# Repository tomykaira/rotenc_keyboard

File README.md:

# rotenc

This is PCB design and example qmk_firmware keymap implementation to add-on rotary encoders (jog dials) to your keyboards.

# Usage

Open EAGLE design file in ./pcb.
I used elecrow to print the board.
I will distribute printed PCBs by 200 JPY + shipping.

Copy keymap to qmk_firmware/keyboards/kets_split/keymaps/foobar and write.

```
make lets_split/rev2:foobar_onehanded:avrdude
```

# REFS

https://www.pixiv.net/fanbox/manage/post/104198
https://twitter.com/tomykaira_2/status/1018332701210783744

# License

keymaps: follow qmk license.
pcb design: public domain.

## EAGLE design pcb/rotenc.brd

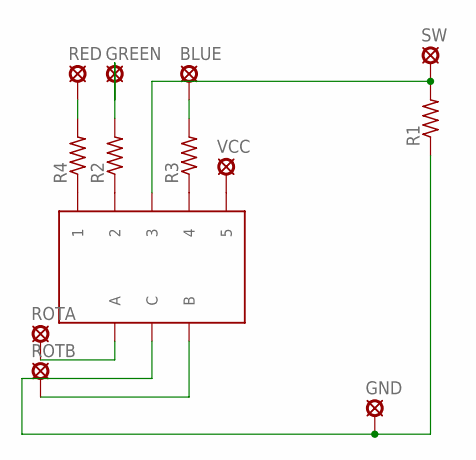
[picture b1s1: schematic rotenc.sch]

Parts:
BLUE: SE13
GND: SE13
GREEN: SE13
R1, R2, R3, R4: R-US_0207/7; 0207/7
RED: SE13
ROTA: SE13
ROTB: SE13
SW: SE13
U$1: EC12PLRGB; EL1296RGB
VCC: SE13

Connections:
BLUE: BLUE.MP, R3.2
GREEN: GREEN.MP, R2.2
unnamed: R2.1, U$1.2
unnamed: R4.1, U$1.1
unnamed: R3.1, U$1.4
unnamed: U$1.5, VCC.MP
unnamed: GND.MP, R1.1, U$1.C
RED: R4.2, RED.MP
ROTA: ROTA.MP, U$1.A
ROTB: ROTB.MP, U$1.B
SW: R1.2, SW.MP, U$1.3

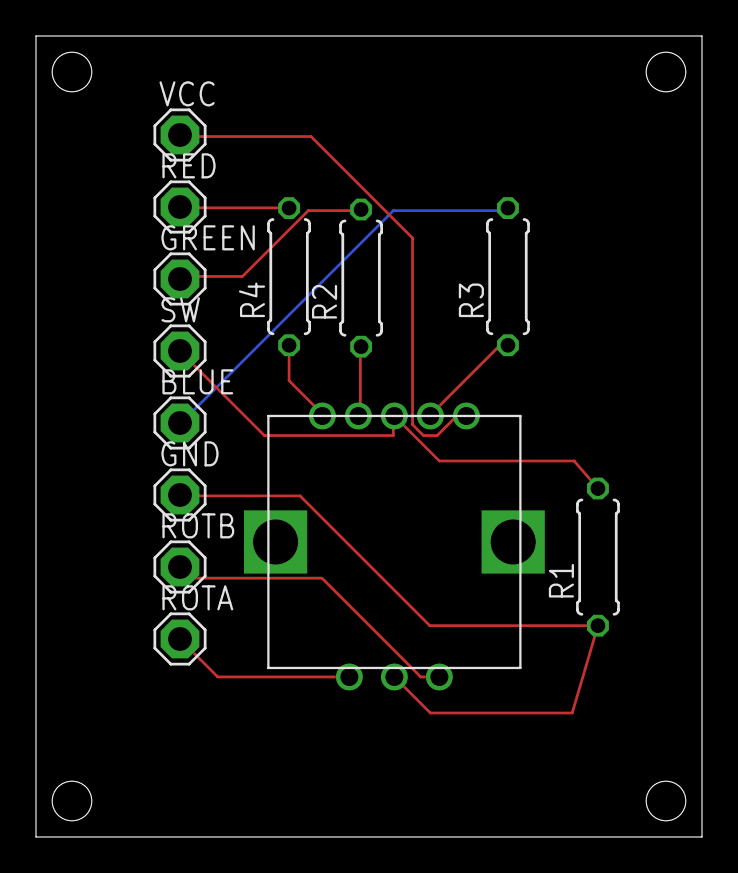
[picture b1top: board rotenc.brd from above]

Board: 2 copper layers, 37.0 x 44.5 mm, 13 parts (0 on the bottom side), 11 nets.

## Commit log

2018-07-16 Init
2018-07-16 Readme
